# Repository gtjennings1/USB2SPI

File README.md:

# USB2SPI
pip3 install pyserial
pip3 install progressbar2

python flasher.py -p COM19 -i RGB_LED_BLINK.hex -o read.bin -b 4 > flasher.log

('under the hood' command examples)
python flash_erase.py -p COM19 -a 0 -s 0

python flash_write.py -p COM19 -a 0 -v 256

python flash_dump.py -p COM19 -a 0 -s 4

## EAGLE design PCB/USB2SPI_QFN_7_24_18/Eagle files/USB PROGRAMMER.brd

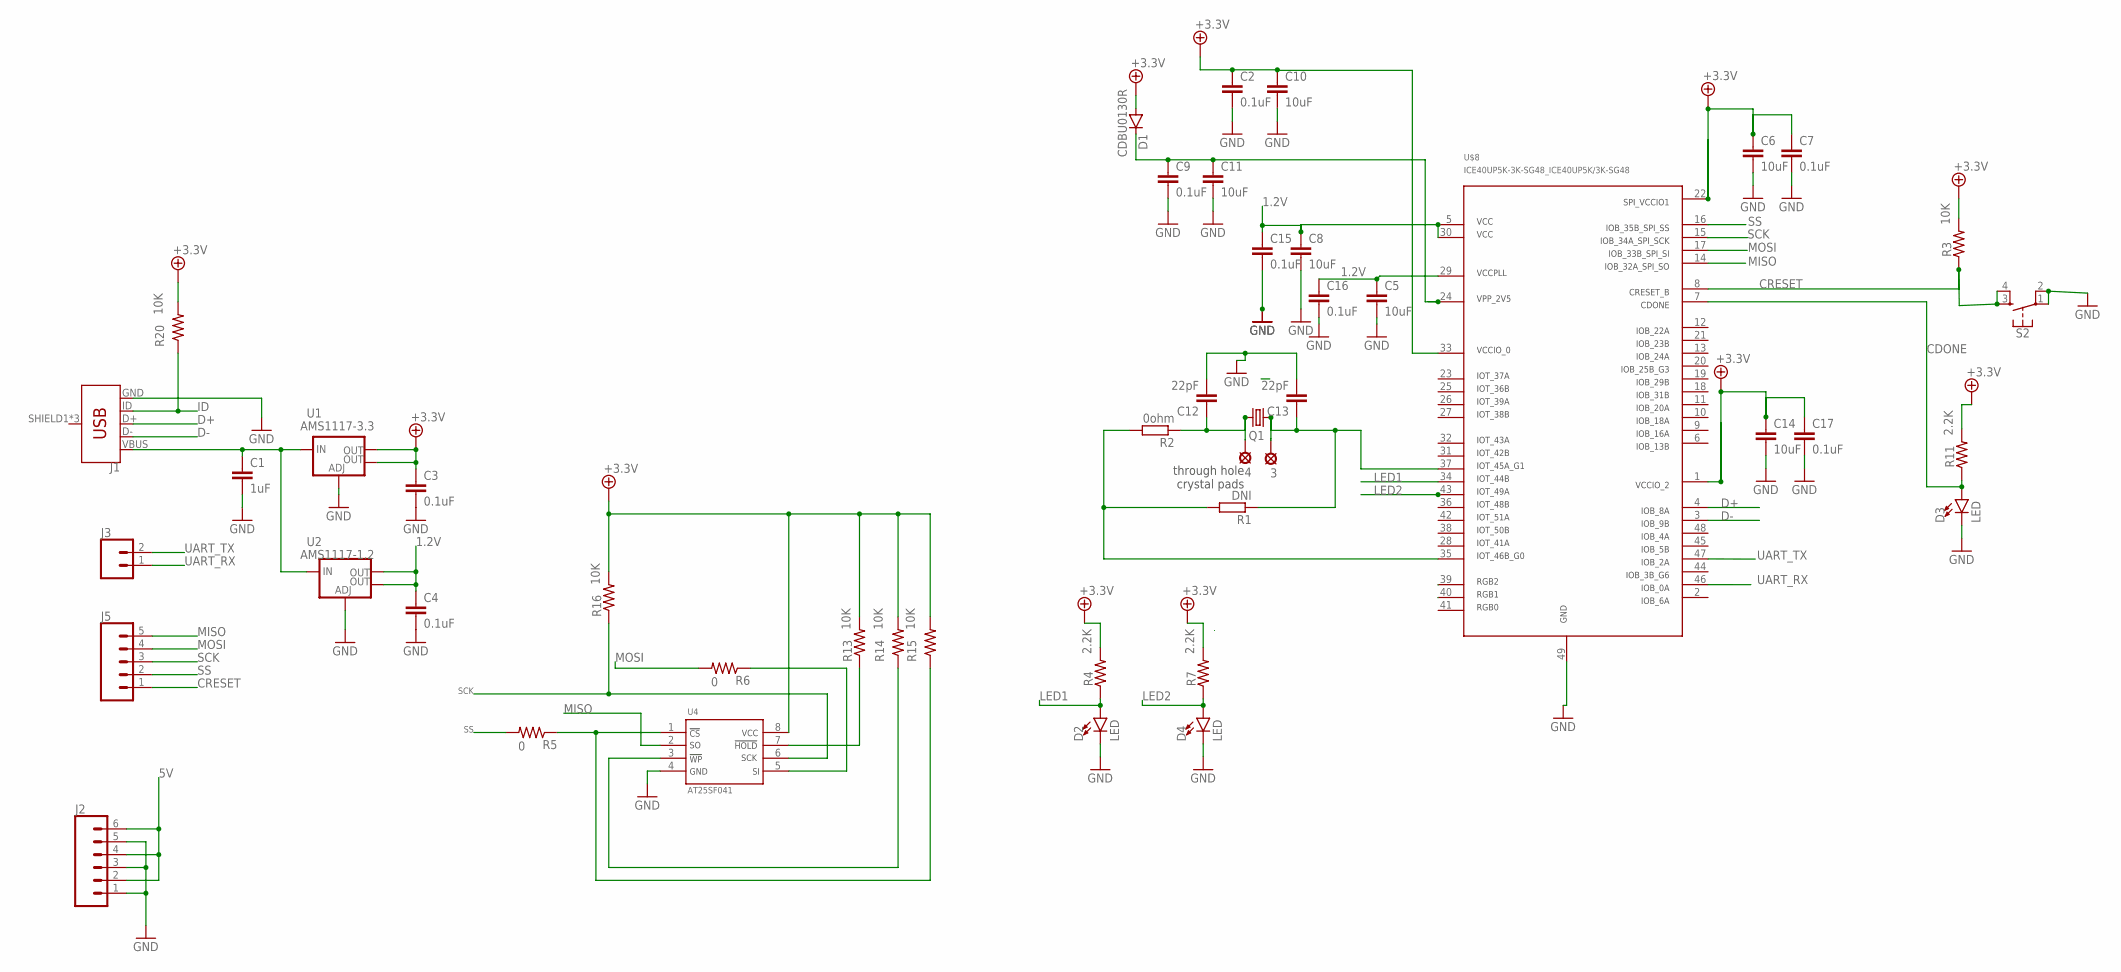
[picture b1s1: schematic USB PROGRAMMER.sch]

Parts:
3, 4: LSP10
C1: 1uF; C0402
C2, C3, C4, C7, C9, C15, C16, C17: 0.1uF; C0402
C5, C6, C8, C10, C11, C14: 10uF; C0402
C12, C13: 22pF; C0402
D1: CDBU0130R; SOD523
D2, D3, D4: LED; LED-0603
J1: USB_MICRO-B_FEMALE-SMT; USB-B-MICRO-SMD
J2: CONN_06NO_SILK_FEMALE_PTH; 1X06_NO_SILK
J3: CONN_02; 1X02
J5: CONN_05; 1X05
Q1: CRYSTALHC49UP; HC49UP
R1: DNI; R0402
R2: 0ohm; R0402
R3, R13, R14, R15, R16, R20: 10K; 0603-RES
R4, R7, R11: 2.2K; 0603-RES
R5, R6: 0; 0805
S2: MOMENTARY-SWITCH-SPST-2-SMD-4.6X2.8MM; TACTILE_SWITCH_SMD_4.6X2.8MM
U1: AMS1117-3.3; SOT223
U2: AMS1117-1.2; SOT223
U4: AT25SF041; SO8
U$8: ICE40UP5K-3K-SG48_ICE40UP5K/3K-SG48

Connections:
1.2V: C4.1, C5.1, C8.1, C15.1, C16.1, U2.2 (OUT), U2.4 (OUT), U$8.5, U$8.29, U$8.30
2: R1.2, R2.2, U$8.35
5V: C1.1, J1.VBUS, J2.2, J2.4, J2.6, U1.3 (IN), U2.3 (IN)
+3.3V: C2.1, C3.1, C6.1, C7.1, C10.1, C14.1, C17.1, D1.A, R3.2, R4.2, R7.2, R11.2, R13.2, R14.2, R15.2, R16.2, R20.2, U1.2 (OUT), U1.4 (OUT), U4.8, U$8.1, U$8.22, U$8.33
CDONE: D3.A, R11.1, U$8.7
CRESET: J5.1, R3.1, S2.3, S2.4, U$8.8
D+: J1.D+, U$8.4
D-: J1.D-, U$8.3
GND: C1.2, C2.2, C3.2, C4.2, C5.2, C6.2, C7.2, C8.2, C9.2, C10.2, C11.2, C12.2, C13.2, C14.2, C15.2, C16.2, C17.2, D2.C, D3.C, D4.C, J1.GND, J2.1, J2.3, J2.5, S2.1, S2.2, U1.1 (ADJ), U2.1 (ADJ), U4.4, U$8.49
ID: J1.ID, R20.1
LED1: D2.A, R4.1, U$8.34
LED2: D4.A, R7.1, U$8.43
MISO: J5.5, U4.2, U$8.14
MOSI: J5.4, R6.2, U$8.17
unnamed: 4.MP, C12.1, Q1.2, R2.1
unnamed: R13.1, U4.7
unnamed: 3.MP, C13.1, Q1.1, R1.1, U$8.37
unnamed: R14.1, U4.3
unnamed: R5.1, R15.1, U4.1
unnamed: C9.1, C11.1, D1.C, U$8.24
unnamed: R6.1, U4.5
SCK: J5.3, R16.1, U4.6, U$8.15
SS: J5.2, R5.2, U$8.16
UART_RX: J3.1, U$8.46
UART_TX: J3.2, U$8.47

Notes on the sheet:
through hole crystal pads

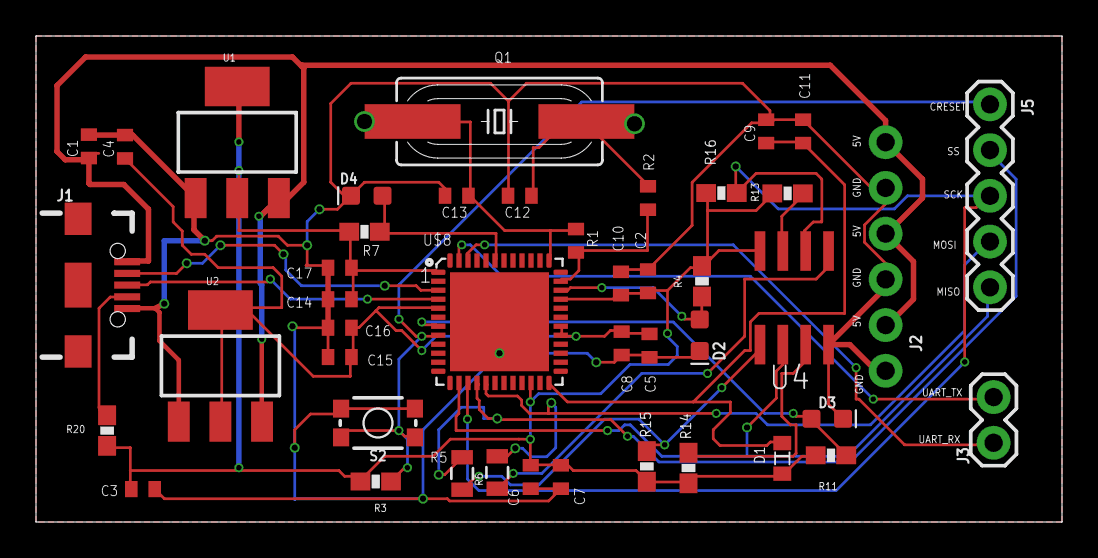
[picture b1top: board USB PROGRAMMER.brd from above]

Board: 2 copper layers, 57.0 x 27.0 mm, 46 parts (0 on the bottom side), 25 nets.

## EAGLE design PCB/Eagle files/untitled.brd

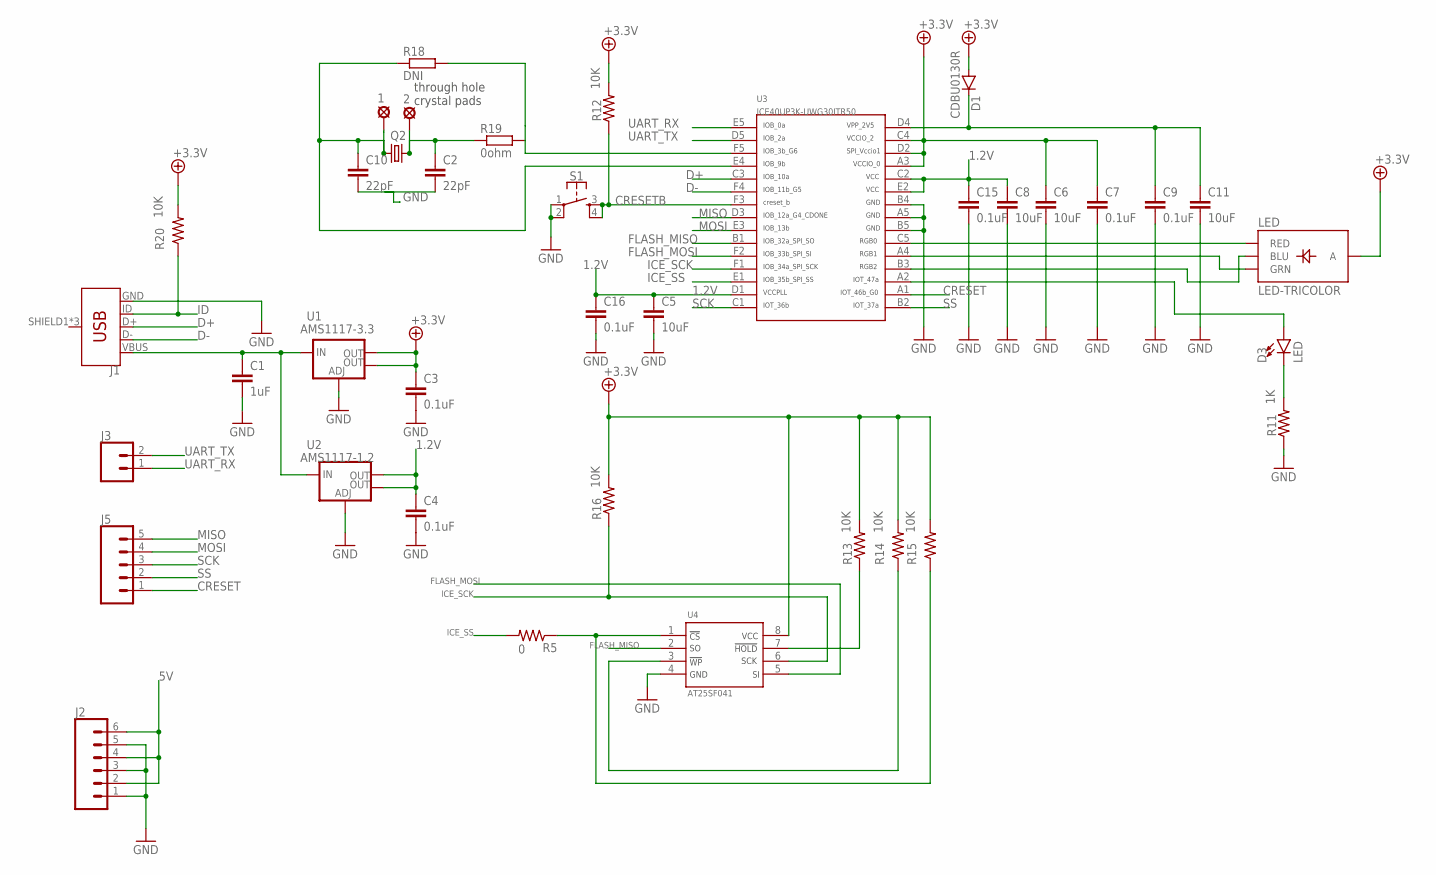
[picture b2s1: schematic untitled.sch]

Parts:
1, 2: LSP10
C1: 1uF; C0402
C2, C10: 22pF; C0402
C3, C4, C7, C9, C15, C16: 0.1uF; C0402
C5, C6, C8, C11: 10uF; C0402
D1: CDBU0130R; SOD523
D3: LED; LED-0603
J1: USB_MICRO-B_FEMALE-SMT; USB-B-MICRO-SMD
J2: CONN_06NO_SILK_FEMALE_PTH; 1X06_NO_SILK
J3: CONN_02; 1X02
J5: CONN_05; 1X05
LED: LED-TRICOLOR; LED-TRICOLOR-SMD
Q2: CRYSTALHC49UP; HC49UP
R5: 0; 0805
R11: 1K; 0603-RES
R12, R13, R14, R15, R16, R20: 10K; 0603-RES
R18: DNI; R0402
R19: 0ohm; R0402
S1: MOMENTARY-SWITCH-SPST-2-SMD-4.6X2.8MM; TACTILE_SWITCH_SMD_4.6X2.8MM
U1: AMS1117-3.3; SOT223
U2: AMS1117-1.2; SOT223
U3: ICE40UP3K-UWG30ITR50; WLSC-30
U4: AT25SF041; SO8

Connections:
1.2V: C4.1, C5.1, C8.1, C15.1, C16.1, U2.2 (OUT), U2.4 (OUT), U3.C2, U3.D1, U3.E2
5: 1.MP, C10.1, Q2.1, R18.1, U3.E4
5V: C1.1, J1.VBUS, J2.2, J2.4, J2.6, U1.3 (IN), U2.3 (IN)
6: R18.2, R19.2, U3.F5
+3.3V: C3.1, C6.1, C7.1, D1.A, LED.A, R12.2, R13.2, R14.2, R15.2, R16.2, R20.2, U1.2 (OUT), U1.4 (OUT), U3.A3, U3.C4, U3.D2, U4.8
CRESET: J5.1, U3.A1
CRESETB: R12.1, S1.3, S1.4, U3.F3
D+: J1.D+, U3.C3
D-: J1.D-, U3.F4
FLASH_MISO: U3.B1, U4.2
FLASH_MOSI: U3.F2, U4.5
GND: C1.2, C2.2, C3.2, C4.2, C5.2, C6.2, C7.2, C8.2, C9.2, C10.2, C11.2, C15.2, C16.2, J1.GND, J2.1, J2.3, J2.5, R11.1, S1.1, S1.2, U1.1 (ADJ), U2.1 (ADJ), U3.A5, U3.B4, U3.B5, U4.4
ICE_SCK: R16.1, U3.F1, U4.6
ICE_SS: R5.2, U3.E1
ID: J1.ID, R20.1
MISO: J5.5, U3.D3
MOSI: J5.4, U3.E3
unnamed: R13.1, U4.7
unnamed: R14.1, U4.3
unnamed: R5.1, R15.1, U4.1
unnamed: LED.R (RED), U3.C5
unnamed: LED.G (GRN), U3.A4
unnamed: LED.B (BLU), U3.B3
unnamed: D3.A, U3.A2
unnamed: D3.C, R11.2
unnamed: C9.1, C11.1, D1.C, U3.D4
unnamed: 2.MP, C2.1, Q2.2, R19.1
SCK: J5.3, U3.C1
SS: J5.2, U3.B2
UART_RX: J3.1, U3.E5
UART_TX: J3.2, U3.D5

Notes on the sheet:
through hole crystal pads

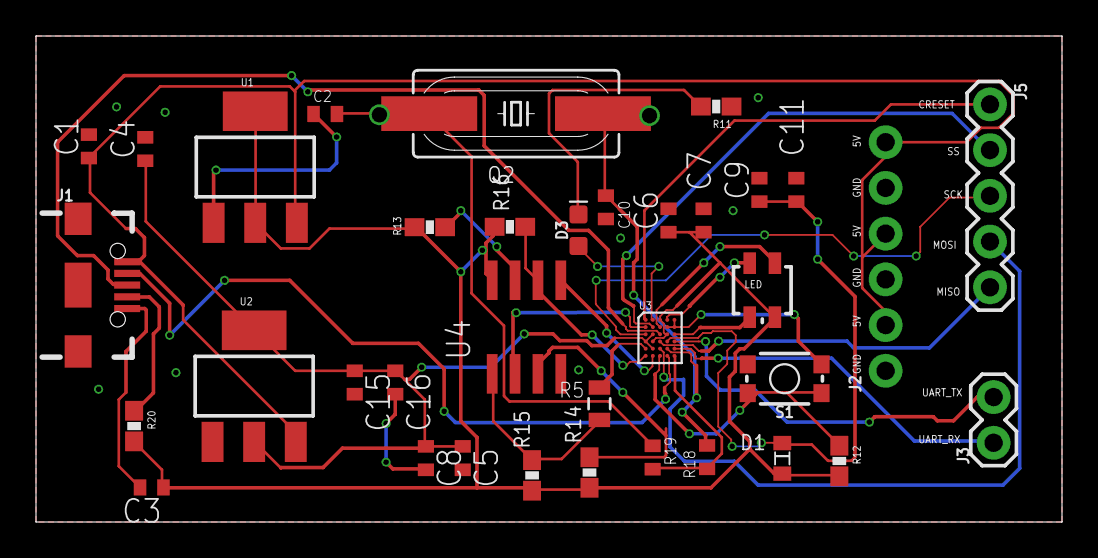
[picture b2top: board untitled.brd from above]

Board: 2 copper layers, 57.0 x 27.0 mm, 38 parts (0 on the bottom side), 31 nets.

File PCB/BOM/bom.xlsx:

Partlist
Exported | from untitled.brd at | 43285.997071759259
EAGLE Ver | sion 6.1.0 Copyright | (c) 1988-2012 CadSoft
Assembly | variant:
Part | Value | Package | Library
C1 | 1uF | C0402 | eagle-ltspice
C2,C10 | 22pF | C0402 | eagle-ltspice
C3,C4 | 0.1uF | C0402 | eagle-ltspice
C5,C6,C8,C11 | 10uF | C0402 | eagle-ltspice
C7,C9,C15,C16 | 0.1uF | C0402 | eagle-ltspice
D1 | CDBU0130R | SOD523 | CDBU0130R
D3 | LED | LED-0603 | SparkFun-LED
J1 | 10118192-0001LF | USB-B-MICRO-SMD | MICRO USB 105164-0001
LED | LED-TRICOLOR | LED-TRICOLOR-SMD | SparkFun-LED
Q2 | FC4SDCBMF24.0-T1 | HC49UP | crystal
R5 | 0 | 805 | SparkFun-Resistors
R11 | 1K | 0603-RES | SparkFun-Resistors
R12,R12,R13,R14,R15,R16 | 10K | 0603-RES | SparkFun-Resistors
R18 | DNI | R0402 | eagle-ltspice
R19 | 0ohm | R0402 | eagle-ltspice
R20 | 10K | 0603-RES | SparkFun-Resistors
S1 | KMR231NG LFS | TACTILE_SWITCH_SMD_4.6X2.8MM | SparkFun-Switches | http://www.ck-components.com/media/1479/kmr2.pdf
U1 | AMS1117-3.3 | SOT223 | SparkFun-IC-Power
U2 | AMS1117-1.2 | SOT223 | SparkFun-IC-Power
U3 | ICE40UP3K-UWG30ITR50 | WLSC-30 | ICE40UP3K
U4 | AT25SF041 | SO8 | AT25SF041

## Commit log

2018-03-09 USB2SPI initial working hardware revision from Rudolph
2018-03-09 Adding XO3LF Starter kit project
2018-03-09 Added sck and ssn to top level port list
2018-03-10 Added SSN to jumper since SSN must be low over the entire transmission. This is a temporary hack to manually control SSN.
2018-03-12 create a package for usb descriptors
2018-03-13 solved a bug with ss_n for continuous data
2018-03-15 added .gitignore and python script
2018-03-19 python script modificationd
2018-03-19 desc_pkg added to XO3 project
2018-03-19 remove unnecessary files from XO3
2018-03-27 added ascii to hex conversion and verification
2018-03-27 xo3l socketed port pinout lpf added more led bitstreams CRESETN pin added synthesis generated files removed
2018-03-28 added spi_ctrl module and correction flash.py
2018-03-29 rebuild XO3 project with spi_ctrl
2018-03-29 usb tx/rx buffer size is increased up to 512 bytes
2018-03-29 update scripts with creset control feature
2018-03-29 experimental read/write code
2018-03-30 spi hold experiment
2018-03-30 added jed
2018-03-30 commit for chekout
2018-04-04 big transfer size
2018-04-04 work copy
2018-04-05 fixed errors
2018-04-05 debug messages removed
2018-04-05 updated readme.md with command examples.
2018-04-05 python script updates
2018-04-05 added install dependencies to readme.md
2018-04-09 setting new reference frequency
2018-04-09 work commit
2018-05-15 added sync for dp and dn ports
2018-05-17 skew fix
2018-05-18 added repeat reading after timeout
2018-05-20 added -d key to flasher
2018-05-22 fixed debug read
2018-05-25 added check written page
2018-07-08 PCB design rev a
2018-07-09 trace width update
2018-07-24 QFN version of board

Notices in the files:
parts and their libraries:
SparkFun-IC-Power: Licensing: Creative Commons ShareAlike 4.0 International - https://creativecommons.org/licenses/by-sa/4.0
